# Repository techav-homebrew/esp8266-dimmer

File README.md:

# esp8266-dimmer
ESP8266 3-Channel LED dimmer

This is a simple WiFi-enabled 3-channel LED dimmer with 4 user buttons. It is designed to be powered from the same 12 Volt power supply that would be used to power a common RGB LED strip. Higher current draw (e.g. longer LED strips) may require active cooling on the output switching transistors. 

This project has been abandoned and is being published here to release into public domain (CC0). Project is intended as an intellectual excercise only, and its author will accept no liability for any adverse effects of its use. 

## Construction
Output screw terminals and programming header are intended to be mounted on the bottom of the board. All other parts should be mounted on top. 

Board is designed to use virtually any capable TO-252-3 transistor. Pads are included for a 100-Ohm base resistor if a bipolar transistor is used. For a MOSFET, this resistor is not necessary, and a jumper or 0-ohm resistor may be installed instead.

## Programming
No firmware currently exists. Device can be programmed with any ESP8266 toolchain, including the Arduino environment. Programs are loaded via 3.3V UART connected to the programming header. To place the device in programming mode, connect the UART, hold the Down button (button 3, GPIO0), and assert ~Reset by connecting to Signal Ground. 

### Programming Header
1. TxD
2. RxD
3. Signal Ground
4. Signal Ground
5. ~Reset

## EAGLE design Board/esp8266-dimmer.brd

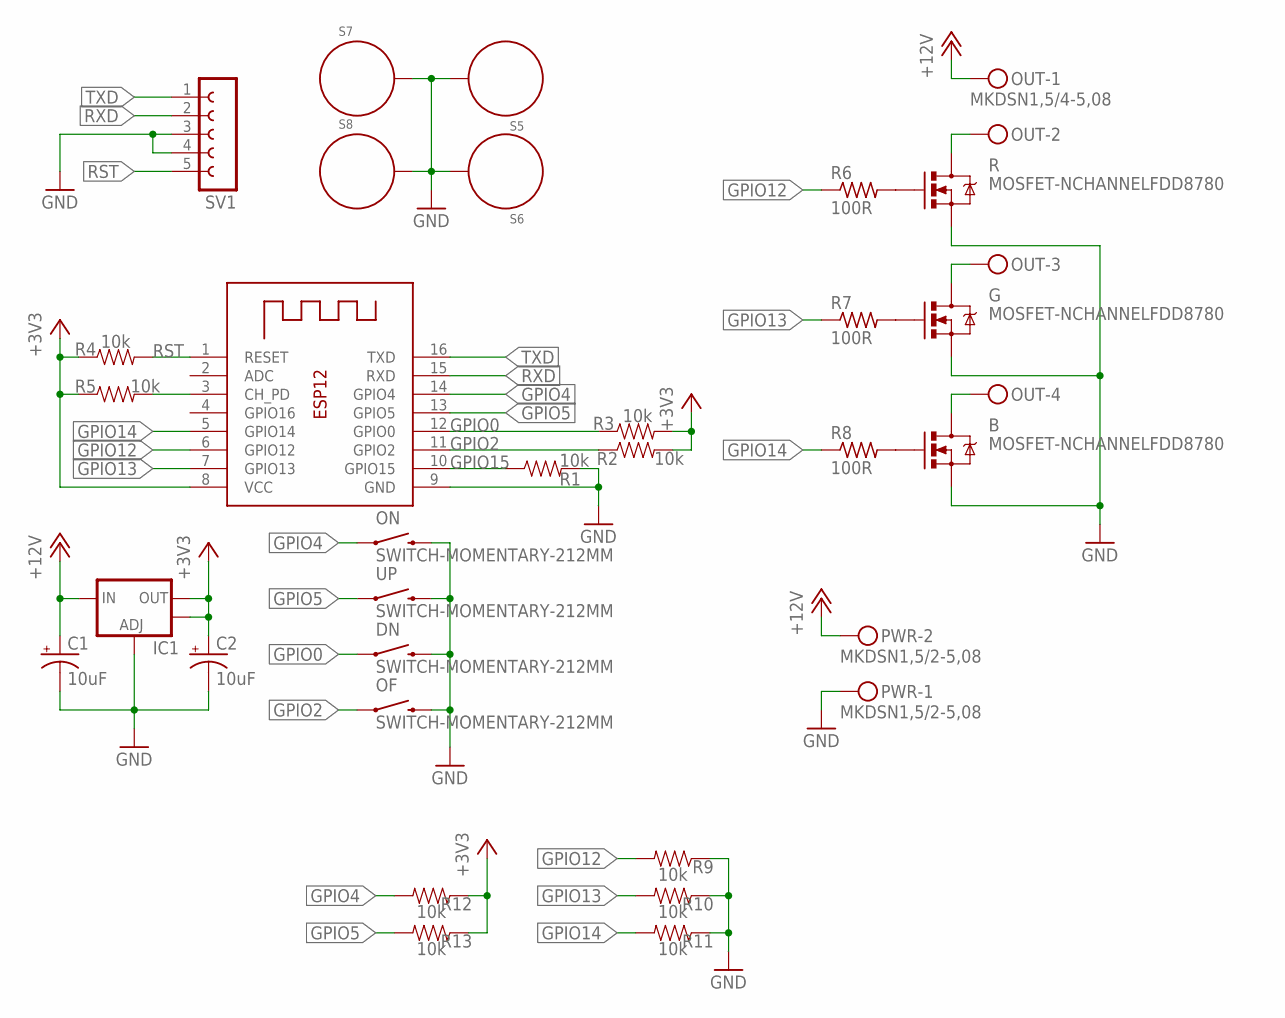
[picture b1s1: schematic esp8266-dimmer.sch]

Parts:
B: MOSFET-NCHANNELFDD8780; DPAK
C1, C2: 10uF; EIA3216-KIT
DN: SWITCH-MOMENTARY-212MM; TACTILE-PTH-12MM
ESP-12E: ESP-12
G: MOSFET-NCHANNELFDD8780; DPAK
IC1: V_REG_LM1117SOT223; SOT223
OF: SWITCH-MOMENTARY-212MM; TACTILE-PTH-12MM
ON: SWITCH-MOMENTARY-212MM; TACTILE-PTH-12MM
OUT: MKDSN1,5/4-5,08
PWR: MKDSN1,5/2-5,08
R: MOSFET-NCHANNELFDD8780; DPAK
R1, R2, R3, R4, R5, R9, R10, R11, R12, R13: 10k; 0805
R6, R7, R8: 100R; 0805-THM-7
S5, S6, S7, S8: STANDOFF_ELECTRICAL; STANDOFF-ELECTRICAL
SV1: FE05W
UP: SWITCH-MOMENTARY-212MM; TACTILE-PTH-12MM

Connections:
+3V3: C2.A (+), ESP-12E.8 (VCC), IC1.2 (OUT), IC1.4 (OUT), R2.2, R3.2, R4.1, R5.1, R12.1, R13.1
+12V: C1.A (+), IC1.3 (IN), OUT.1, PWR.2
BOUT: B.4 (D), OUT.4
GND: B.3 (S), C1.C (-), C2.C (-), DN.3 (2), ESP-12E.9 (GND), G.3 (S), IC1.1 (ADJ), OF.3 (2), ON.3 (2), PWR.1, R.3 (S), R1.2, R9.1, R10.1, R11.1, S5.P1, S6.P1, S7.P1, S8.P1, SV1.3, SV1.4, UP.3 (2)
GOUT: G.4 (D), OUT.3
GPIO0: DN.1, ESP-12E.12 (GPIO0), R3.1
GPIO2: ESP-12E.11 (GPIO2), OF.1, R2.1
GPIO4: ESP-12E.14 (GPIO4), ON.1, R12.2
GPIO5: ESP-12E.13 (GPIO5), R13.2, UP.1
GPIO12: ESP-12E.6 (GPIO12), R6.1, R9.2
GPIO13: ESP-12E.7 (GPIO13), R7.1, R10.2
GPIO14: ESP-12E.5 (GPIO14), R8.1, R11.2
GPIO15: ESP-12E.10 (GPIO15), R1.1
unnamed: B.1 (G), R8.2
unnamed: G.1 (G), R7.2
unnamed: R.1 (G), R6.2
unnamed: ESP-12E.3 (CH_PD), R5.2
ROUT: OUT.2, R.4 (D)
RST: ESP-12E.1 (RESET), R4.2, SV1.5
RXD: ESP-12E.15 (RXD), SV1.2
TXD: ESP-12E.16 (TXD), SV1.1

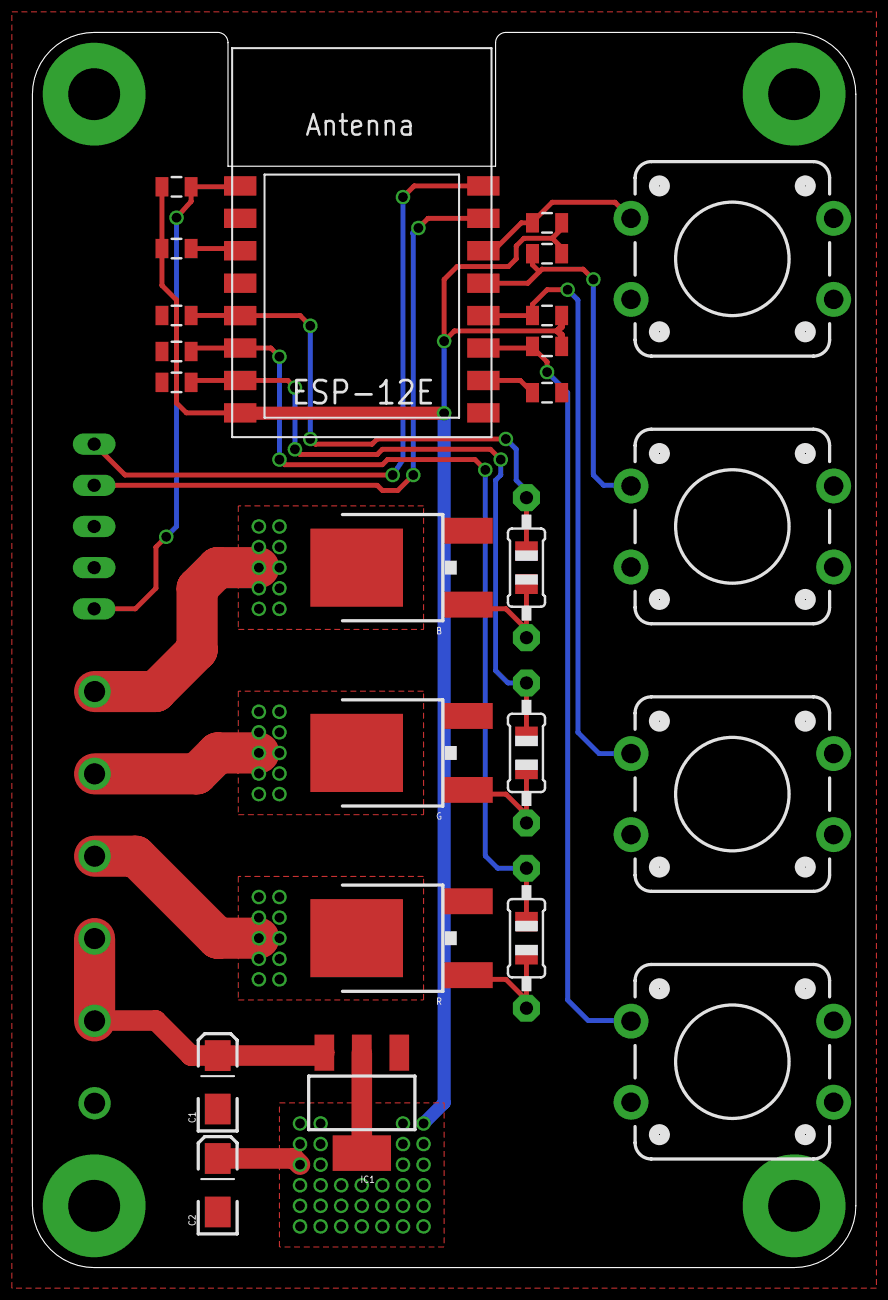
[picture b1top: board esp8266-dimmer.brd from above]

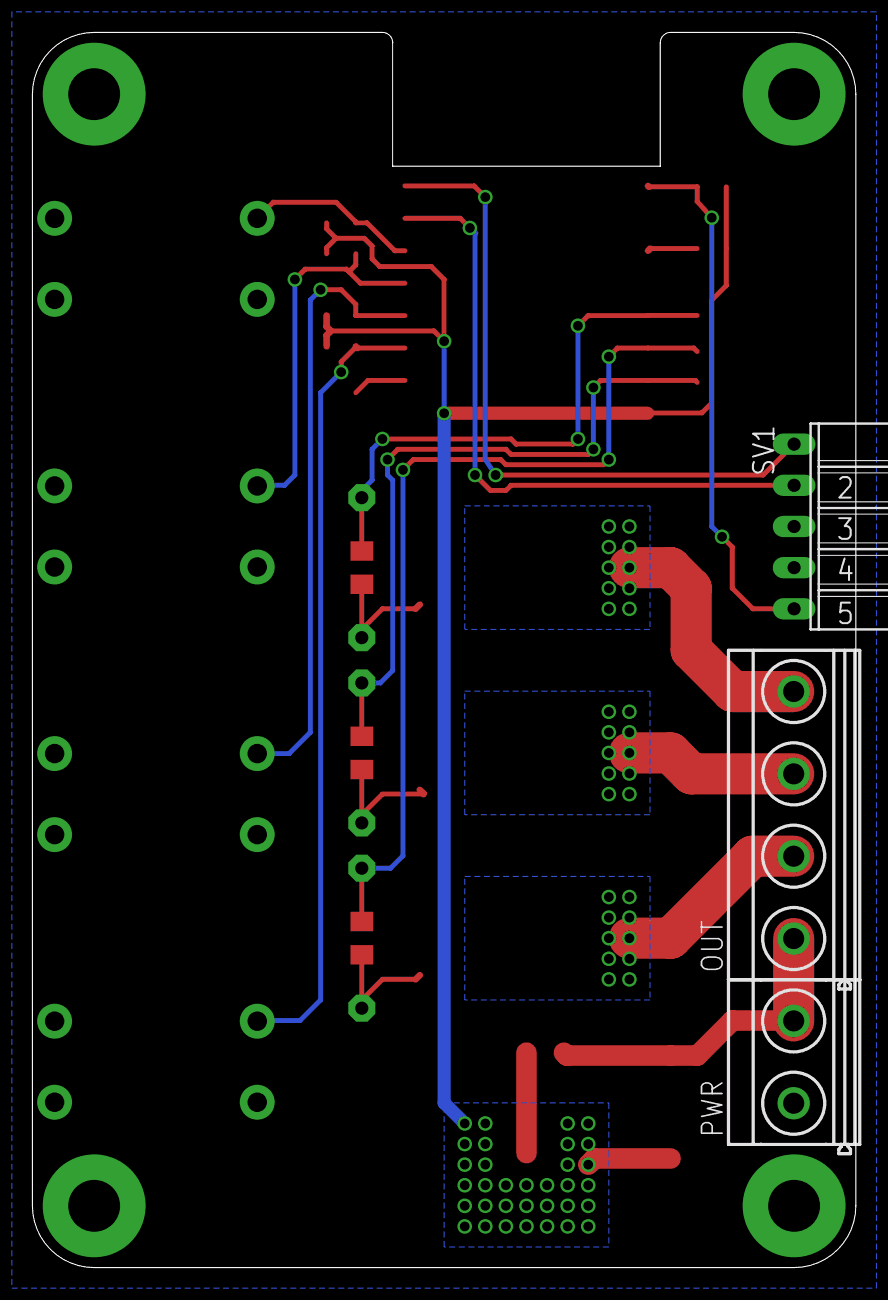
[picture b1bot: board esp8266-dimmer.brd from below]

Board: 2 copper layers, 50.8 x 76.2 mm, 31 parts (3 on the bottom side), 21 nets.

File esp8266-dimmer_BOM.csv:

Part,Value,Device,Package,Description
R,N-CHANNEL,NTD4969NT4G,TO-252-3,N-Channel MOSFET
G,N-CHANNEL,NTD4969NT4G,TO-252-3,N-Channel MOSFET
B,N-CHANNEL,NTD4969NT4G,TO-252-3,N-Channel MOSFET
C1,10uF,CAP_POL1206-KIT,EIA3216-KIT,Tantalum Capacitor Polarized
C2,10uF,CAP_POL1206-KIT,EIA3216-KIT,Tantalum Capacitor Polarized
ESP-12E,ESP-12E,ESP-12,ESP-12,ESP8266 Module
IC1,LM1117,AZ1117CH-3.3TRG1,SOT223,3.3V Voltage Regulator LM1117
ON,SWITCH-MOMENTARY-212MM,SWITCH-MOMENTARY-212MM,TACTILE-PTH-12MM,12mm Tactile Switch with Button Cap
UP,SWITCH-MOMENTARY-212MM,SWITCH-MOMENTARY-212MM,TACTILE-PTH-12MM,12mm Tactile Switch with Button Cap
DN,SWITCH-MOMENTARY-212MM,SWITCH-MOMENTARY-212MM,TACTILE-PTH-12MM,12mm Tactile Switch with Button Cap
OF,SWITCH-MOMENTARY-212MM,SWITCH-MOMENTARY-212MM,TACTILE-PTH-12MM,12mm Tactile Switch with Button Cap
OUT,"MKDSN1,5/4-5,08","MKDSN1,5/4-5,08","MKDSN1,5/4-5,08",4-Contact Screw Terminal
PWR,"MKDSN1,5/2-5,08","MKDSN1,5/2-5,08","MKDSN1,5/2-5,08",2-Contact Screw Terminal
R1,10k,RK73B2ATTD103J,0805,10k-Ohm Resistor
R2,10k,RK73B2ATTD103J,0805,10k-Ohm Resistor
R3,10k,RK73B2ATTD103J,0805,10k-Ohm Resistor
R4,10k,RK73B2ATTD103J,0805,10k-Ohm Resistor
R5,10k,RK73B2ATTD103J,0805,10k-Ohm Resistor
R6,0R,RK73Z2ATTD,0805,0-Ohm Resistor (Jumper)
R7,0R,RK73Z2ATTD,0805,0-Ohm Resistor (Jumper)
R8,0R,RK73Z2ATTD,0805,0-Ohm Resistor (Jumper)
R9,10k,RK73B2ATTD103J,0805,10k-Ohm Resistor
R10,10k,RK73B2ATTD103J,0805,10k-Ohm Resistor
R11,10k,RK73B2ATTD103J,0805,10k-Ohm Resistor
R12,10k,RK73B2ATTD103J,0805,10k-Ohm Resistor
R13,10k,RK73B2ATTD103J,0805,10k-Ohm Resistor
SV1,,FE05W,FE05W,5x1 Right-Angle Header

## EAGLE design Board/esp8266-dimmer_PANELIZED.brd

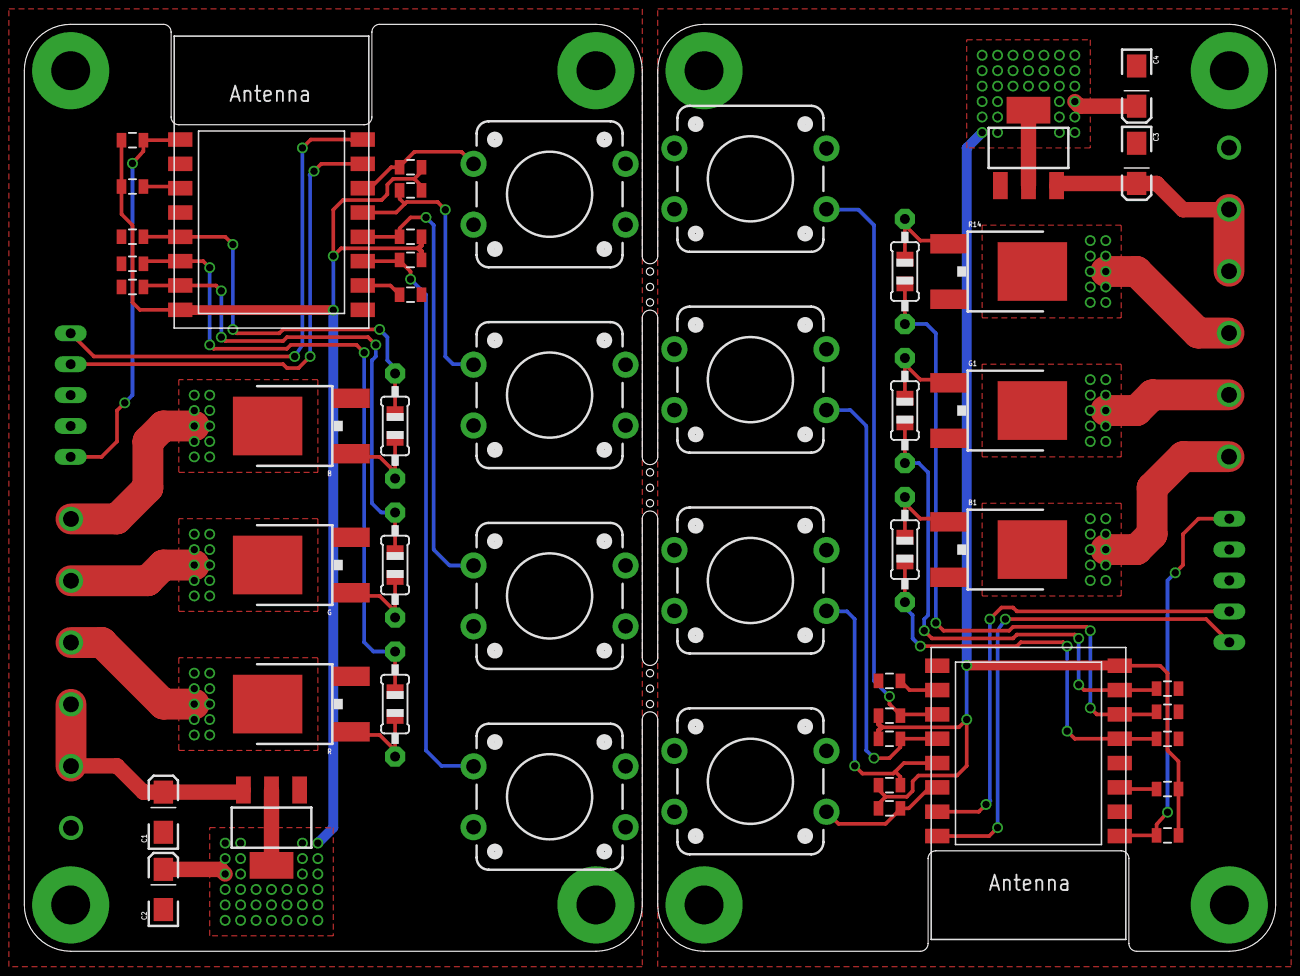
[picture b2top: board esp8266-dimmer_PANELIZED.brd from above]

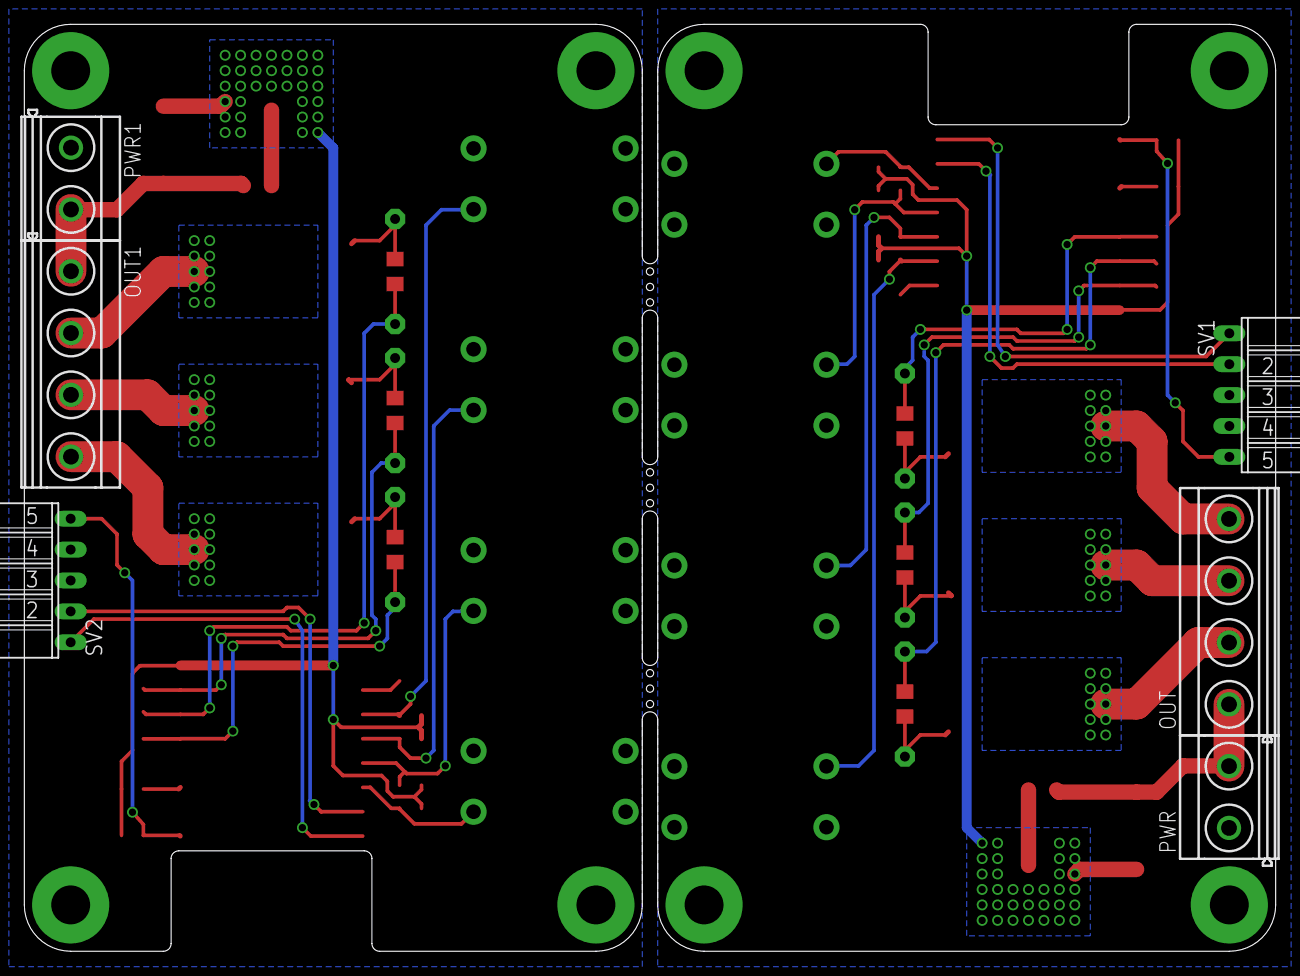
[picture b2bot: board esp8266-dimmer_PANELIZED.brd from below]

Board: 2 copper layers, 102.9 x 76.2 mm, 62 parts (6 on the bottom side), 42 nets.

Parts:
B, B1: MOSFET-NCHANNELFDD8780; DPAK
C1, C2, C3, C4: 10uF; EIA3216-KIT
DN, DN1: SWITCH-MOMENTARY-212MM; TACTILE-PTH-12MM
ESP-12E, ESP-12E1: ESP-12
G, G1: MOSFET-NCHANNELFDD8780; DPAK
IC1, IC2: SOT223
OF, OF1: SWITCH-MOMENTARY-212MM; TACTILE-PTH-12MM
ON, ON1: SWITCH-MOMENTARY-212MM; TACTILE-PTH-12MM
OUT, OUT1: MKDSN1,5/4-5,08
PWR, PWR1: MKDSN1,5/2-5,08
R, R14: MOSFET-NCHANNELFDD8780; DPAK
R1, R2, R3, R4, R5, R9, R10, R11, R12, R13, R15, R16, R17, R18, R19, R23, R24, R25, R26, R27: 10k; 0805
R6, R7, R8, R20, R21, R22: 100R; 0805-THM-7
S1, S2, S3, S4, S5, S6, S7, S8: STANDOFF_ELECTRICAL; STANDOFF-ELECTRICAL
SV1, SV2: FE05W
UP, UP1: SWITCH-MOMENTARY-212MM; TACTILE-PTH-12MM

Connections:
+3V1: C4.A, ESP-12E1.8, IC2.2, IC2.4, R16.2, R17.2, R18.1, R19.1, R26.1, R27.1
+3V3: C2.A, ESP-12E.8, IC1.2, IC1.4, R2.2, R3.2, R4.1, R5.1, R12.1, R13.1
+12V: C1.A, IC1.3, OUT.1, PWR.2
+12V1: C3.A, IC2.3, OUT1.1, PWR1.2
BOUT: B.4, OUT.4
BOUT1: B1.4, OUT1.4
GND: B.3, C1.C, C2.C, DN.3, ESP-12E.9, G.3, IC1.1, OF.3, ON.3, PWR.1, R.3, R1.2, R9.1, R10.1, R11.1, S5.P1, S6.P1, S7.P1, S8.P1, SV1.3, SV1.4, UP.3
GND1: B1.3, C3.C, C4.C, DN1.3, ESP-12E1.9, G1.3, IC2.1, OF1.3, ON1.3, PWR1.1, R14.3, R15.2, R23.1, R24.1, R25.1, S1.P1, S2.P1, S3.P1, S4.P1, SV2.3, SV2.4, UP1.3
GOUT: G.4, OUT.3
GOUT1: G1.4, OUT1.3
GPIO0: DN.1, ESP-12E.12, R3.1
GPIO1: ESP-12E1.10, R15.1
GPIO2: ESP-12E.11, OF.1, R2.1
GPIO3: ESP-12E1.11, OF1.1, R16.1
GPIO4: ESP-12E.14, ON.1, R12.2
GPIO5: ESP-12E.13, R13.2, UP.1
GPIO6: DN1.1, ESP-12E1.12, R17.1
GPIO7: ESP-12E1.13, R27.2, UP1.1
GPIO8: ESP-12E1.14, ON1.1, R26.2
GPIO9: ESP-12E1.5, R22.1, R25.2
GPIO10: ESP-12E1.6, R20.1, R23.2
GPIO11: ESP-12E1.7, R21.1, R24.2
GPIO12: ESP-12E.6, R6.1, R9.2
GPIO13: ESP-12E.7, R7.1, R10.2
GPIO14: ESP-12E.5, R8.1, R11.2
GPIO15: ESP-12E.10, R1.1
unnamed: ESP-12E1.3, R19.2
unnamed: B.1, R8.2
unnamed: G.1, R7.2
unnamed: R.1, R6.2
unnamed: ESP-12E.3, R5.2
unnamed: B1.1, R22.2
unnamed: G1.1, R21.2
unnamed: R14.1, R20.2
ROUT: OUT.2, R.4
ROUT1: OUT1.2, R14.4
RST: ESP-12E.1, R4.2, SV1.5
RST1: ESP-12E1.1, R18.2, SV2.5
RXD: ESP-12E.15, SV1.2
RXD1: ESP-12E1.15, SV2.2
TXD: ESP-12E.16, SV1.1
TXD1: ESP-12E1.16, SV2.1

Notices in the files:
parts and their libraries:
SparkFun-Passives: Licensing: Creative Commons ShareAlike 4.0 International - https://creativecommons.org/licenses/by-sa/4.0
